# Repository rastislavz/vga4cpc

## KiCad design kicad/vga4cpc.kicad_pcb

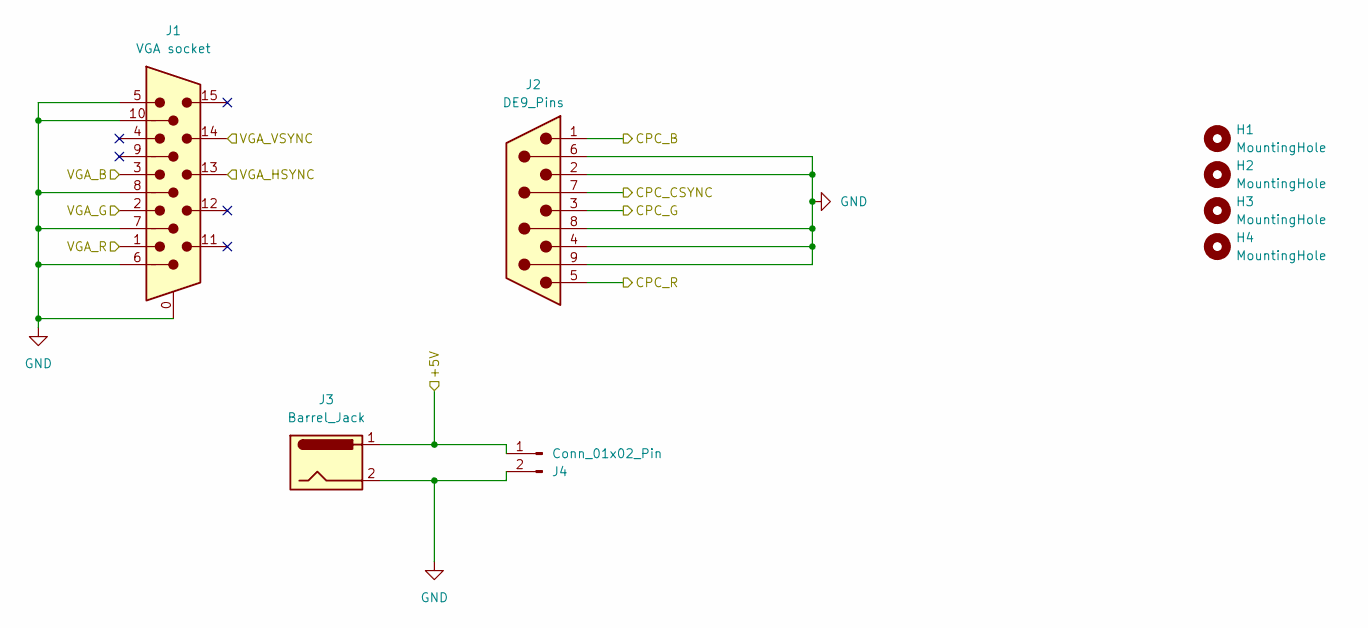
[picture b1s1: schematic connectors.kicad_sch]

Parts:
H1, H2, H3, H4: MountingHole; MountingHole_3.2mm_M3
J1: VGA socket; DSUB-15-HD_Socket_Horizontal_P2.29x2.54mm_EdgePinOffset8.35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
J2: DE9_Pins; DSUB-9_Pins_Horizontal_P2.77x2.54mm_EdgePinOffset9.40mm
J3: Barrel_Jack; BarrelJack_Horizontal
J4: Conn_01x02_Pin; JST_XH_S2B-XH-A_1x02_P2.50mm_Horizontal

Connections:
+5V: J3.1, J4.1; also elsewhere on the board
/Comparators/CPC_B: J2.1; also elsewhere on the board
/Comparators/CPC_G: J2.3; also elsewhere on the board
/Comparators/CPC_R: J2.5; also elsewhere on the board
/Connectors/CPC_CSYNC: J2.7; also elsewhere on the board
/Connectors/VGA_B: J1.3; also elsewhere on the board
/Connectors/VGA_G: J1.2; also elsewhere on the board
/Connectors/VGA_HSYNC: J1.13; also elsewhere on the board
/Connectors/VGA_R: J1.1; also elsewhere on the board
/Connectors/VGA_VSYNC: J1.14; also elsewhere on the board
GND: J1.0, J1.5, J1.6, J1.7, J1.8, J1.10, J2.2, J2.4, J2.6, J2.8, J2.9, J3.2, J4.2; also elsewhere on the board

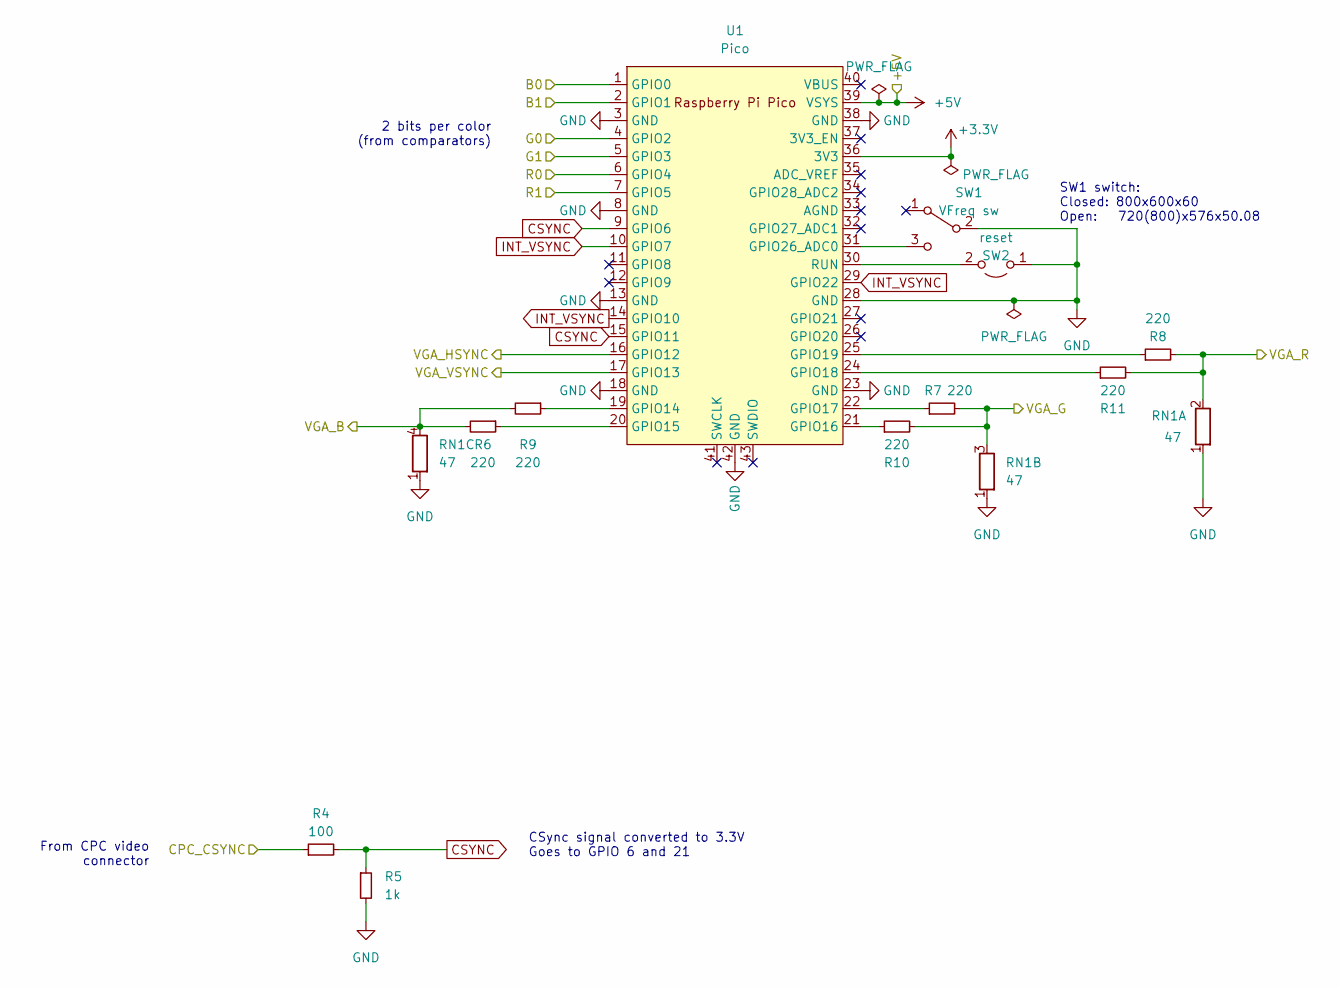
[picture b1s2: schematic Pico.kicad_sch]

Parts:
R4: 100; R_Axial_DIN0204_L3.6mm_D1.6mm_P5.08mm_Horizontal
R5: 1k; R_Axial_DIN0204_L3.6mm_D1.6mm_P5.08mm_Horizontal
R6, R7, R8, R9, R10, R11: 220; R_Axial_DIN0204_L3.6mm_D1.6mm_P5.08mm_Horizontal
RN1: 47; R_Array_SIP4
SW1: VFreq sw; SW_Slide_SPDT_Angled_CK_OS102011MA1Q
SW2: reset; SW_Tactile_SKHH_Angled
U1: Pico; RaspberryPi_Pico_Common_THT_b

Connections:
+3.3V: U1.36 (3V3); also elsewhere on the board
+5V: U1.39 (VSYS); also elsewhere on the board
/Comparators/B0: U1.1 (GPIO0); also elsewhere on the board
/Comparators/B1: U1.2 (GPIO1); also elsewhere on the board
/Comparators/G0: U1.4 (GPIO2); also elsewhere on the board
/Comparators/G1: U1.5 (GPIO3); also elsewhere on the board
/Comparators/R0: U1.6 (GPIO4); also elsewhere on the board
/Comparators/R1: U1.7 (GPIO5); also elsewhere on the board
/Connectors/CPC_CSYNC: R4.1; also elsewhere on the board
/Connectors/VGA_B: R6.2, R9.2, RN1.4 (R3.2); also elsewhere on the board
/Connectors/VGA_G: R7.2, R10.2, RN1.3 (R2.2); also elsewhere on the board
/Connectors/VGA_HSYNC: U1.16 (GPIO12); also elsewhere on the board
/Connectors/VGA_R: R8.2, R11.2, RN1.2 (R1.2); also elsewhere on the board
/Connectors/VGA_VSYNC: U1.17 (GPIO13); also elsewhere on the board
CSYNC: R4.2, R5.1, U1.9 (GPIO6), U1.15 (GPIO11)
GND: R5.2, RN1.1 (R1), SW1.2 (B), SW2.1 (A), U1.3 (GND), U1.8 (GND), U1.13 (GND), U1.18 (GND), U1.23 (GND), U1.28 (GND), U1.38 (GND), U1.42 (GND); also elsewhere on the board
INT_VSYNC: U1.10 (GPIO7), U1.14 (GPIO10), U1.29 (GPIO22)
unnamed: SW1.3 (C), U1.31 (GPIO26_ADC0)
unnamed: SW2.2 (B), U1.30 (RUN)
unnamed: R9.1, U1.19 (GPIO14)
unnamed: R6.1, U1.20 (GPIO15)
unnamed: R10.1, U1.21 (GPIO16)
unnamed: R7.1, U1.22 (GPIO17)
unnamed: R11.1, U1.24 (GPIO18)
unnamed: R8.1, U1.25 (GPIO19)

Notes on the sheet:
CSync signal converted to 3.3V Goes to GPIO 6 and 21
SW1 switch: Closed: 800x600x60 Open: 720(800)x576x50.08
2 bits per color (from comparators)
From CPC video connector

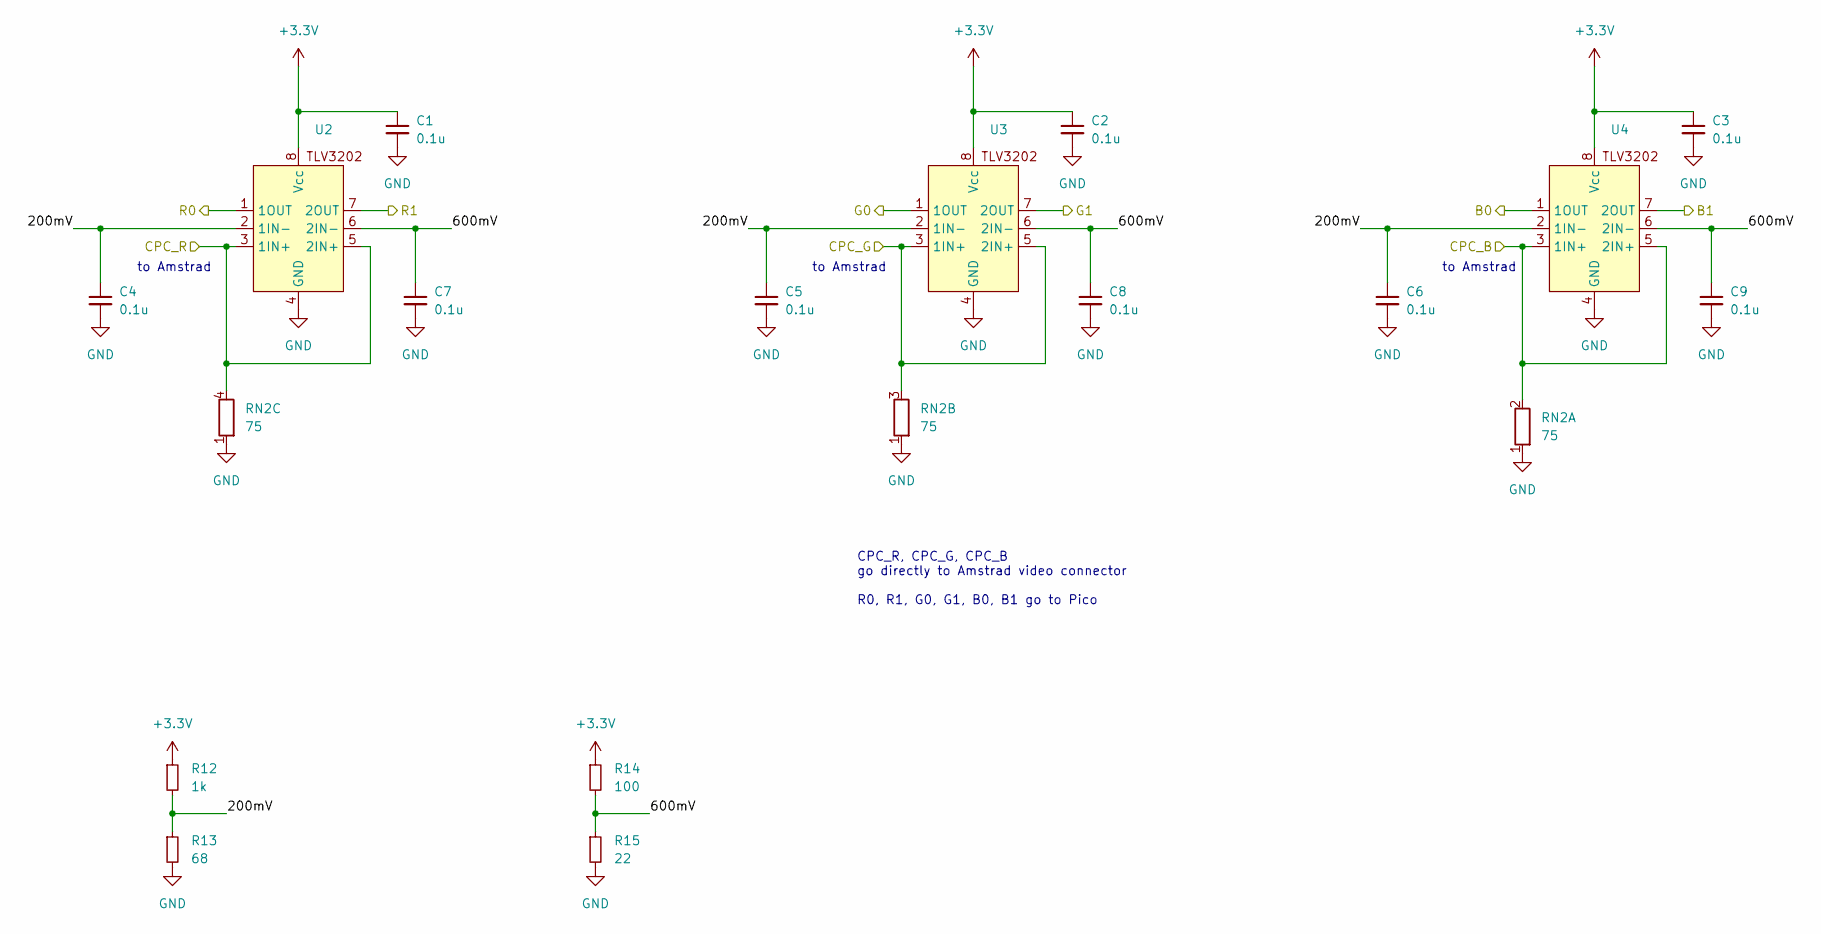
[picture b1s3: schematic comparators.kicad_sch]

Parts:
C1, C2, C3, C4, C5, C6, C7, C8, C9: 0.1u; C_1206_3216Metric_Pad1.33x1.80mm_HandSolder
R12: 1k; R_Axial_DIN0204_L3.6mm_D1.6mm_P5.08mm_Horizontal
R13: 68; R_Axial_DIN0204_L3.6mm_D1.6mm_P5.08mm_Horizontal
R14: 100; R_Axial_DIN0204_L3.6mm_D1.6mm_P5.08mm_Horizontal
R15: 22; R_Axial_DIN0204_L3.6mm_D1.6mm_P5.08mm_Horizontal
RN2: 75; R_Array_SIP4
U2, U3, U4: SOIC-8_3.9x4.9mm_P1.27mm

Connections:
+3.3V: C1.1, C2.1, C3.1, R12.1, R14.1, U2.8 (Vcc), U3.8 (Vcc), U4.8 (Vcc); also elsewhere on the board
/Comparators/200mV: C4.1, C5.1, C6.1, R12.2, R13.1, U2.2 (1IN-), U3.2 (1IN-), U4.2 (1IN-)
/Comparators/600mV: C7.1, C8.1, C9.1, R14.2, R15.1, U2.6 (2IN-), U3.6 (2IN-), U4.6 (2IN-)
/Comparators/B0: U4.1 (1OUT); also elsewhere on the board
/Comparators/B1: U4.7 (2OUT); also elsewhere on the board
/Comparators/CPC_B: RN2.2 (R1.2), U4.3 (1IN+), U4.5 (2IN+); also elsewhere on the board
/Comparators/CPC_G: RN2.3 (R2.2), U3.3 (1IN+), U3.5 (2IN+); also elsewhere on the board
/Comparators/CPC_R: RN2.4 (R3.2), U2.3 (1IN+), U2.5 (2IN+); also elsewhere on the board
/Comparators/G0: U3.1 (1OUT); also elsewhere on the board
/Comparators/G1: U3.7 (2OUT); also elsewhere on the board
/Comparators/R0: U2.1 (1OUT); also elsewhere on the board
/Comparators/R1: U2.7 (2OUT); also elsewhere on the board
GND: C1.2, C2.2, C3.2, C4.2, C5.2, C6.2, C7.2, C8.2, C9.2, R13.2, R15.2, RN2.1 (R1), U2.4 (GND), U3.4 (GND), U4.4 (GND); also elsewhere on the board

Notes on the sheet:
to Amstrad
CPC_R, CPC_G, CPC_B go directly to Amstrad video connector R0, R1, G0, G1, B0, B1 go to Pico

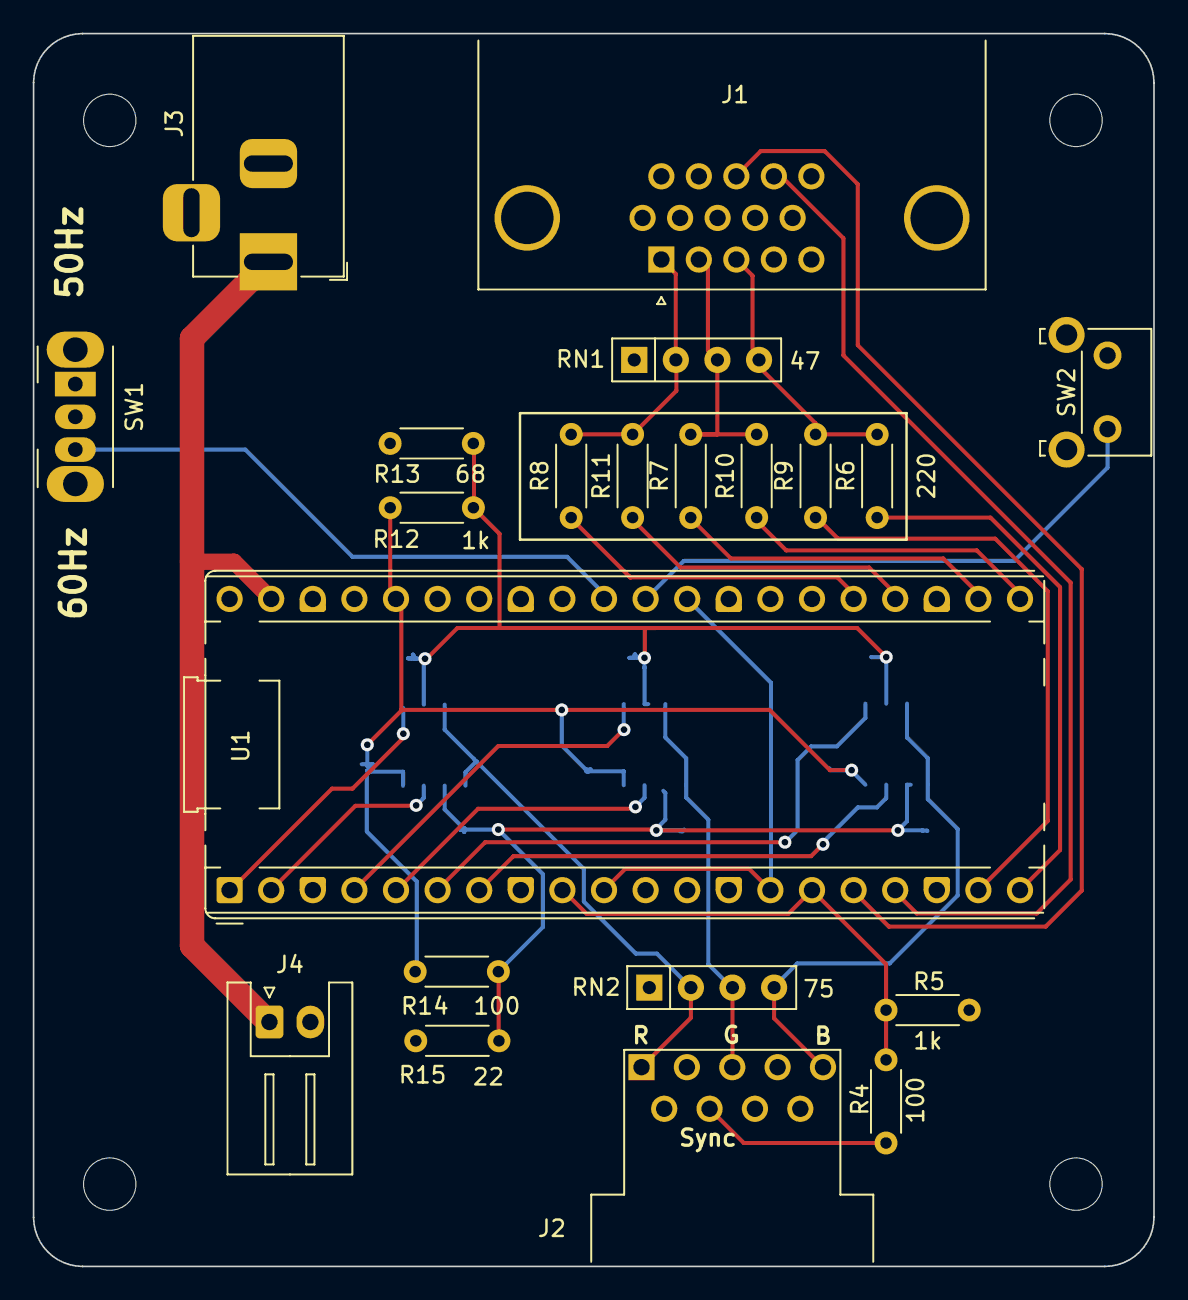
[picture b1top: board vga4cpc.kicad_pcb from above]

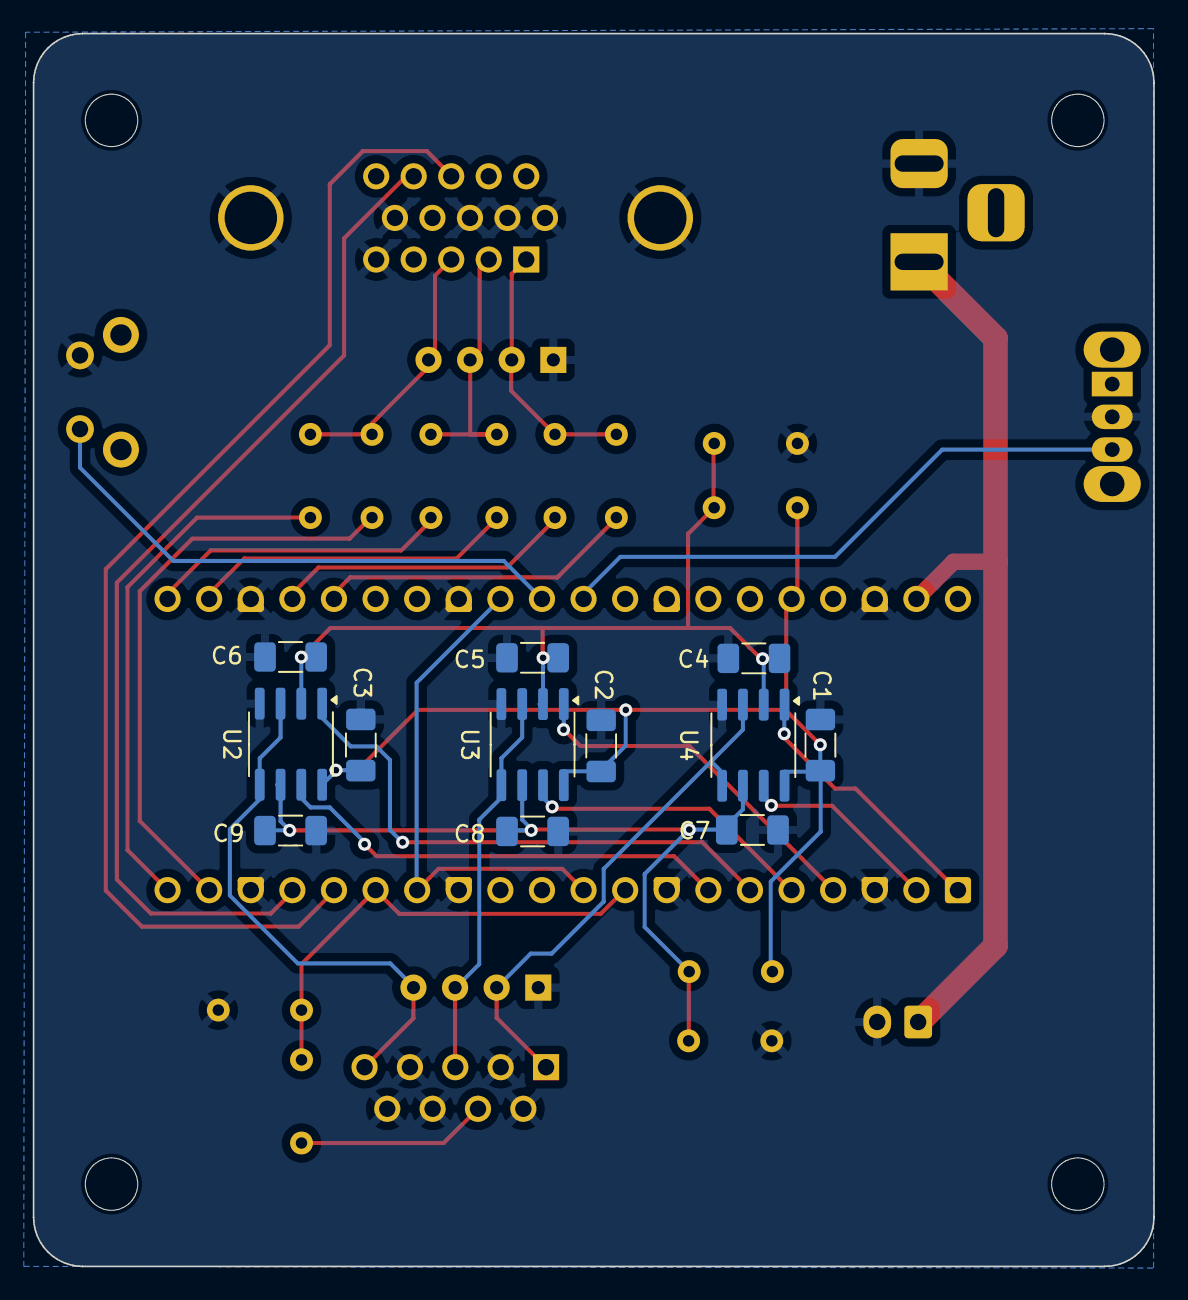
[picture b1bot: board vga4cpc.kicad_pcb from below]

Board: 2 copper layers, 68.4 x 75.3 mm, 37 parts (12 on the bottom side), 30 nets.

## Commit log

2025-09-25 Refactored
2025-09-25 Rotated
